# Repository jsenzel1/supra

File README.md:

# SUPRA
 [SUPRA](https://suprasynth.site/)

is multimode Eurorack module with 4 different experiments in long term time. you can run up to 2 modes at once. use the 4 way joystick and buttons to interact with the modes on the oled

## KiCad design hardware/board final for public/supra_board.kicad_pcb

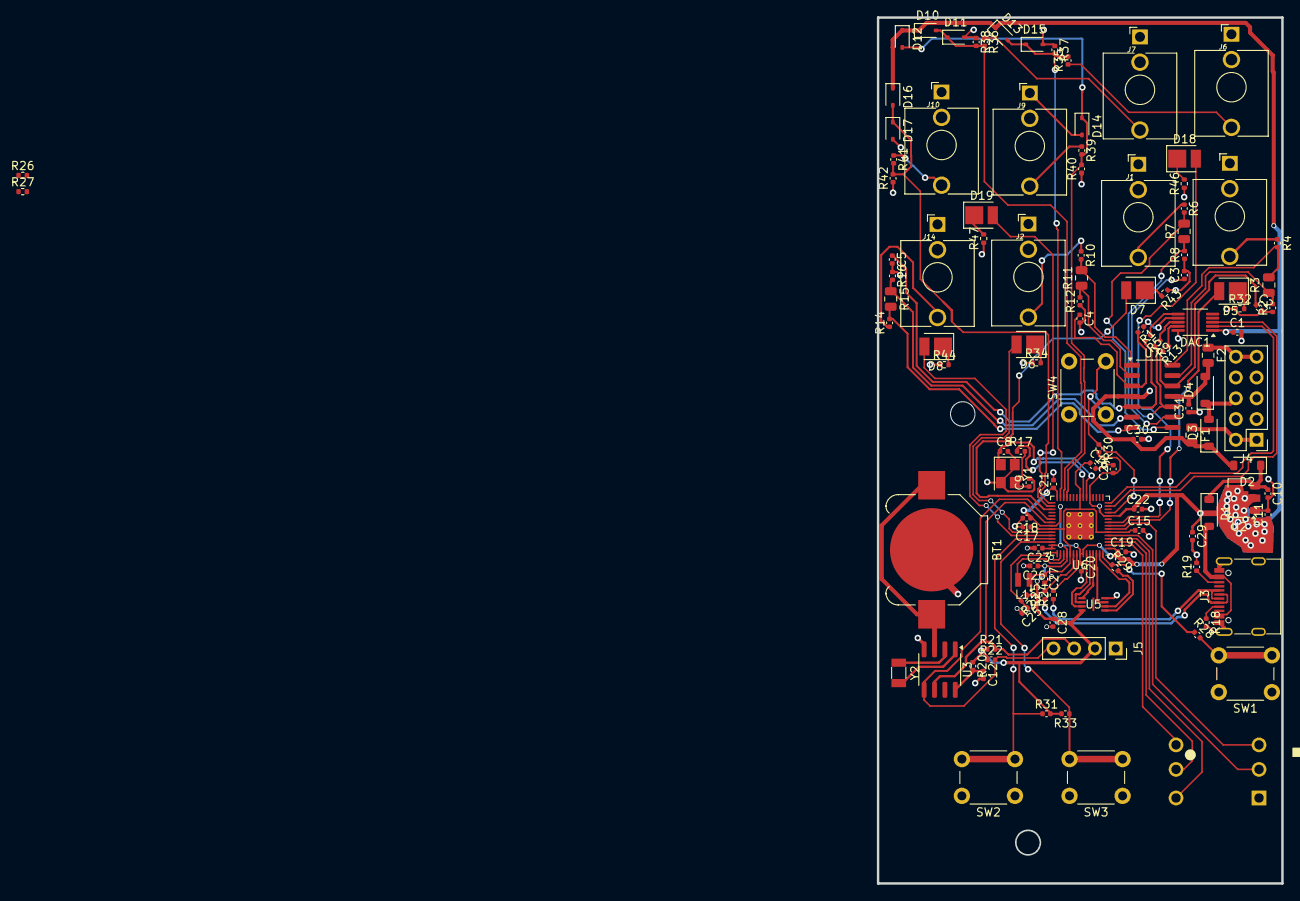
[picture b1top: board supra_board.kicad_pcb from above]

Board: 2 copper layers, 49.5 x 106.0 mm, 119 parts (1 on the bottom side), 84 nets.

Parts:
BT1: Battery_Cell; BatteryHolder_Keystone_3000_1x12mm
C1, C2, C3, C4, C5, C15, C17, C18, C19, C20, C21, C22, C23, C24, C28, C30, C31: 100n; C_0402_1005Metric
C8, C9: 27p; C_0402_1005Metric
C10, C11, C12, C29: 10u; C_0402_1005Metric
C16, C25, C26, C27: 4.7u; C_0402_1005Metric
D1, D2: 5819; D_SOD-123
D3, D4: SM4001; D_SOD-123
D5, D7: R2; LED_PLCC_2835
D6: L2; LED_PLCC_2835
D8: L1; LED_PLCC_2835
D10, D11, D12, D13, D14, D15, D16, D17: BAT43W-V; D_SOD-323
D18: Lselect; LED_PLCC_2835
D19: Rselect; LED_PLCC_2835
DAC1: MCP4728; MSOP-10_3x3mm_P0.5mm
F1, F2: SMD0805P010TF polyfuse; Fuse_0805_2012Metric
J1: out 3; _Jack_3.5mm_QingPu_JACK_ANCHOR
J2: out 2; _Jack_3.5mm_QingPu_JACK_ANCHOR
J3: USB_C_Receptacle_USB2.0; USB_C_Receptacle_G-Switch_GT-USB-7010ASV
J4: Conn_02x05; PinHeader_2x05_P2.54mm_Vertical
J5: OLED DISP; PinSocket_1x04_P2.54mm_Vertical
J6, J7, J9, J10: AudioJack2; _Jack_3.5mm_QingPu_JACK_ANCHOR
J8: out 4; _Jack_3.5mm_QingPu_JACK_ANCHOR
J14: out 1; _Jack_3.5mm_QingPu_JACK_ANCHOR
L1: 3.3u; L_pol_2016
R1, R4, R5, R6, R9, R10, R13, R14, R17, R20, R28: 1k; C_0402_1005Metric
R2, R8, R12, R16: 100k; C_0402_1005Metric
R3, R7, R11, R15: 400k; C_0805_2012Metric
R18, R19: 5.1k; C_0402_1005Metric
R21, R22: 10k; C_0402_1005Metric
R23: 33; R_0402_1005Metric
R24, R25: 27; R_0402_1005Metric
R26, R27: DNF; R_0402_1005Metric
R29: 1k; R_0402_1005Metric
R30, R31, R33: 10K; C_0402_1005Metric
R32, R34, R43, R44: 3.3k; R_0402_1005Metric
R35, R36, R39, R41: 470; C_0402_1005Metric
R37, R38, R40, R42: 100K; C_0402_1005Metric
R46, R47: 100r; R_0402_1005Metric
S1: JS5208; sw_nav_5waySUPRA
SW1: btnBOOT; SW_PUSH_6mm
SW2: btnA; SW_PUSH_6mm
SW3: btnB; SW_PUSH_6mm
SW4: btnHand; SW_PUSH_6mm
U2: LD1117S33CTR; SOT-89-3
U3: PCF8523T; SOIC-8_3.9x4.9mm_P1.27mm
U5: W25Q128JVS; SON50P300X200X60-9N
U6: RP2350_60QFN; RP2350-QFN-60-1EP_7x7_P0.4mm_EP3.4x3.4mm_ThermalVias
U7: OPA1679; SOIC-14_3.9x8.7mm_P1.27mm
Y1: X322512MSB4SI (mini 12MhZ crystal); Crystal_SMD_3225-4Pin_3.2x2.5mm
Y2: Crystal DST310S 32.768KHz; Crystal_SMD_3215-2Pin_3.2x1.5mm

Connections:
+1V1: C15.1, C16.1, C17.1, C27.1, L1.1, U6.6 (DVDD), U6.23 (DVDD), U6.39 (DVDD), U6.50 (VREG_FB)
+3V3: C1.1, C11.1, C18.1, C19.1, C20.1, C21.1, C22.1, C23.1, C24.1, C26.1, C28.1, C29.1, D10.1 (K), D12.1 (K), D13.1 (K), D16.1 (K), DAC1.1 (VDD), J5.2, R20.1, R21.1, R22.1, R23.1, R30.2, R31.2, R33.2, U2.2 (VOUT), U5.8 (VCC), U6.1 (IOVDD), U6.11 (IOVDD), U6.20 (IOVDD), U6.30 (IOVDD), U6.38 (IOVDD), U6.44 (ADC_AVDD), U6.45 (IOVDD), U6.49 (VREG_VIN), U6.53 (USB_OTP_VDD), U6.54 (QSPI_IOVDD)
+12V-buffered: C30.1, D2.2 (A), D3.1 (K), F1.2, U7.4 (V+)
-12V: C31.2, D4.2 (A), F2.2, U7.11 (V-)
/FLASH_SS: R29.2, U5.1 (~CS)
/QSPI_SCLK: U5.6 (CLK), U6.56 (QSPI_SCLK)
/QSPI_SD0: U5.5 (DI(IO0)), U6.57 (QSPI_SD0)
/QSPI_SD1: U5.2 (DO(IO1)), U6.59 (QSPI_SD1)
/QSPI_SD2: U5.3 (IO2), U6.58 (QSPI_SD2)
/QSPI_SD3: U5.7 (IO3), U6.55 (QSPI_SD3)
/QSPI_SS: R28.1, R29.1, U6.60 (QSPI_SS)
/VREG_AVDD: C25.1, R23.2, U6.46 (VREG_AVDD)
/VREG_LX: L1.2, U6.48 (VREG_LX)
/~USB_BOOT: R28.2, SW1.2
DAC_SCL: DAC1.2 (SCL), U6.15 (GPIO11)
DAC_SDA: DAC1.3 (SDA), U6.14 (GPIO10)
GND: BT1.2 (-), C1.2, C2.2, C3.2, C4.2, C5.2, C8.2, C9.2, C10.2, C11.2, C12.2, C15.2, C16.2, C17.2, C18.2, C19.2, C20.2, C21.2, C22.2, C23.2, C24.2, C25.2, C26.2, C27.2, C28.2, C29.2, C30.2, C31.1, D3.2 (A), D4.1 (K), D11.2 (A), D14.2 (A), D15.2 (A), D17.2 (A), DAC1.10 (VSS), J1.S, J2.S, J3.A1 (GND), J3.A12 (GND), J3.B1 (GND), J3.B12 (GND), J3.S1 (SHIELD), J4.3, J4.4, J4.5, J4.6, J4.7, J4.8, J5.1, J6.S, J7.S, J8.S, J9.S, J10.S, J14.S, R2.1, R8.1, R12.1, R16.1, R18.2, R19.2, R32.1, R34.1, R37.1, R38.1, R40.1, R42.1, R43.1, R44.1, R46.1, R47.1, S1.1, SW1.1, SW2.1, SW3.1, SW4.1, U2.1 (GND), U3.4 (VSS), U5.4 (GND), U6.47 (VREG_PGND), U6.61 (GND), Y1.2, Y1.4
LEDL1: D8.2 (A), U6.41 (GPIO27_ADC1)
LEDL2: D6.2 (A), U6.40 (GPIO26_ADC0)
LEDLsel: D18.2 (A), U6.9 (GPIO6)
LEDR1: D7.2 (A), U6.33 (GPIO21)
LEDR2: D5.2 (A), U6.8 (GPIO5)
LEDRsel: D19.2 (A), U6.32 (GPIO20)
unnamed: BT1.1 (+), U3.3 (VBAT)
unnamed: C9.1, R17.2, Y1.3
unnamed: C10.1, D1.1 (K), D2.1 (K), U2.3 (VIN)
unnamed: D5.1 (K), R32.2
unnamed: D6.1 (K), R34.2
unnamed: D7.1 (K), R43.2
unnamed: D8.1 (K), R44.2
unnamed: D18.1 (K), R46.2
unnamed: D19.1 (K), R47.2
unnamed: DAC1.6 (VOUTA), R5.1
unnamed: DAC1.7 (VOUTB), R1.1
unnamed: DAC1.8 (VOUTC), R9.1
unnamed: DAC1.9 (VOUTD), R13.1
unnamed: J1.T, R6.1
unnamed: J2.T, R10.1
unnamed: F1.1, J4.1, J4.2
unnamed: F2.1, J4.9, J4.10
unnamed: J6.T, R35.1
unnamed: J7.T, R36.1
unnamed: J8.T, R4.1
unnamed: J9.T, R39.1
unnamed: J10.T, R41.1
unnamed: J14.T, R14.1
unnamed: R3.2, R4.2, U7.14
unnamed: R6.2, R7.2, U7.8
unnamed: R10.2, R11.2, U7.1
unnamed: R14.2, R15.2, U7.7
unnamed: U3.1 (OSCI), Y2.1
unnamed: U3.2 (OSCO), Y2.2
unnamed: C12.1, R20.2, U3.8 (VDD)
unnamed: R25.2, U6.51 (USB_DM)
unnamed: R24.2, U6.52 (USB_DP)
unnamed: C4.1, R1.2, U7.3 (+)
unnamed: R11.1, R12.2, U7.2 (-)
unnamed: C5.1, R5.2, U7.5 (+)
unnamed: R15.1, R16.2, U7.6 (-)
unnamed: C3.1, R9.2, U7.10 (+)
unnamed: R7.1, R8.2, U7.9 (-)
unnamed: C2.1, R13.2, U7.12 (+)
unnamed: R2.2, R3.1, U7.13 (-)
SCL_BUS: J5.3, R21.2, U3.6 (SCL), U6.37 (GPIO25)
SDA_BUS: J5.4, R22.2, U3.5 (SDA), U6.36 (GPIO24)
btnA: R31.1, SW2.2, U6.42 (GPIO28_ADC2)
btnB: R33.1, SW3.2, U6.43 (GPIO29_ADC3)
btnHand: R30.1, SW4.2, U6.12 (GPIO8)
cc1: J3.A5 (CC1), R18.1
cc2: J3.B5 (CC2), R19.1
crystalin: C8.1, U6.21 (XIN), Y1.1
crystalout: R17.1, U6.22 (XOUT)
in1: D13.2 (A), D15.1 (K), R35.2, R37.2, U6.29 (GPIO18)
in2: D10.2 (A), D11.1 (K), R36.2, R38.2, U6.28 (GPIO17)
in3: D12.2 (A), D14.1 (K), R39.2, R40.2, U6.27 (GPIO16)
in4: D16.2 (A), D17.1 (K), R41.2, R42.2, U6.31 (GPIO19)
nav1: S1.2, U6.5 (GPIO3)
nav2: S1.4, U6.2 (GPIO0)
nav3: S1.5, U6.3 (GPIO1)
nav4: S1.6, U6.4 (GPIO2)
nav5: S1.3, U6.7 (GPIO4)
usbC_vBus: D1.2 (A), J3.A4 (VBUS), J3.A9 (VBUS), J3.B4 (VBUS), J3.B9 (VBUS)
usbd+: J3.A6 (D+), J3.B6 (D+), R24.1
usbd-: J3.A7 (D-), J3.B7 (D-), R25.1

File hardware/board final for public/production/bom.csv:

Designator,Footprint,Quantity,Value,LCSC Part #
BT1,BatteryHolder_Keystone_3000_1x12mm,1,Battery_Cell,C964818
"C1, C15, C17, C18, C19, C2, C20, C21, C22, C23, C24, C28, C3, C30, C31, C4, C5",0402,17,100n,C1525
"C10, C11, C12, C29",0402,4,10u,C15525
"C16, C25, C26, C27",0402,4,4.7u,C23733
"C8, C9",0402,2,27p,C1557
"D1, D2",D_SOD-123,2,5819,C8598
"D10, D11, D12, D13, D14, D15, D16, D17",D_SOD-323,8,BAT43W-V,C134399
D18,LED_PLCC_2835,1,Lselect,C7500124
D19,LED_PLCC_2835,1,Rselect,C7500124
"D3, D4",D_SOD-123,2,SM4001,C151781
"D5, D7",LED_PLCC_2835,2,R2,C7500124
D6,LED_PLCC_2835,1,L2,C7500124
D8,LED_PLCC_2835,1,L1,C7500124
DAC1,MSOP-10_3x3mm_P0.5mm,1,MCP4728,C108207
"F1, F2",0805,2,SMD0805P010TF polyfuse,C20975
J1,_Jack_3.5mm_QingPu_JACK_ANCHOR,1,out 3,
"J10, J6, J7, J9",_Jack_3.5mm_QingPu_JACK_ANCHOR,4,AudioJack2,
J14,_Jack_3.5mm_QingPu_JACK_ANCHOR,1,out 1,
J2,_Jack_3.5mm_QingPu_JACK_ANCHOR,1,out 2,
J3,USB_C_Receptacle_G-Switch_GT-USB-7010ASV,1,USB_C_Receptacle_USB2.0,C2988369
J4,PinHeader_2x05_P2.54mm_Vertical,1,Conn_02x05,
J5,PinSocket_1x04_P2.54mm_Vertical,1,OLED DISP,
J8,_Jack_3.5mm_QingPu_JACK_ANCHOR,1,out 4,
L1,L_pol_2016,1,3.3u,C42411119
"R1, R10, R13, R14, R17, R20, R28, R4, R5, R6, R9",0402,11,1k,C11702
"R11, R15, R3, R7",0805,4,400k,
"R12, R16, R2, R37, R38, R40, R42, R8",0402,8,100k,C25741
"R18, R19",0402,2,5.1k,C25905
"R21, R22, R30, R31, R33",0402,5,10k,C25744
R23,0402,1,33,C25105
"R24, R25",0402,2,27,C25100
"R26, R27",0402,2,DNF,
R29,0402,1,1k,
"R32, R34, R43, R44",0402,4,3.3k,C25890
"R35, R36, R39, R41",0402,4,470,C25117
"R46, R47",0402,2,100r,C25076
S1,sw_nav_5waySUPRA,1,JS5208,
SW1,SW_PUSH_6mm,1,btnBOOT,
SW2,SW_PUSH_6mm,1,btnA,
SW3,SW_PUSH_6mm,1,btnB,
SW4,SW_PUSH_6mm,1,btnHand,
U2,SOT-89-3,1,LD1117S33CTR,C81768
U3,SOIC-8_3.9x4.9mm_P1.27mm,1,PCF8523T,C2651516
U5,SON50P300X200X60-9N,1,W25Q128JVS,C2843335
U6,RP2350-QFN-60-1EP_7x7_P0.4mm_EP3.4x3.4mm_ThermalVias,1,RP2350_60QFN,C42411118
U7,SOIC-14_3.9x8.7mm_P1.27mm,1,OPA1679,C2878631
Y1,Crystal_SMD_3225-4Pin_3.2x2.5mm,1,X322512MSB4SI (mini 12MhZ crystal),C20625731
Y2,Crystal_SMD_3215-2Pin_3.2x1.5mm,1,Crystal DST310S 32.768KHz,C93232

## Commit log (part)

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2025-11-18 Create internal ordering guide for SUPRA
    This document serves as an internal ordering guide for SUPRA, detailing the steps to order necessary components and parts.
2025-12-26 Update order guide with shipping note and details
    Added note about fast shipping for display order and provided additional context for joystick toppers.
2026-02-09 added short history
2026-02-12 Revise README with project details and images
    Updated project title and added a description of the SUPRA module.
2026-02-19 Add initial assembly guide content
2026-02-19 assembly guide placeholder
    Added detailed assembly instructions and images for components including joystick and screen.
2026-02-20 Update assembly guide with additional instructions
    Added instructions for joystick cap, battery orientation, and firmware flashing process.
2026-04-12 Build documentation update to clarify the joystick footprint misalignment
2026-04-29 add firmware complete
